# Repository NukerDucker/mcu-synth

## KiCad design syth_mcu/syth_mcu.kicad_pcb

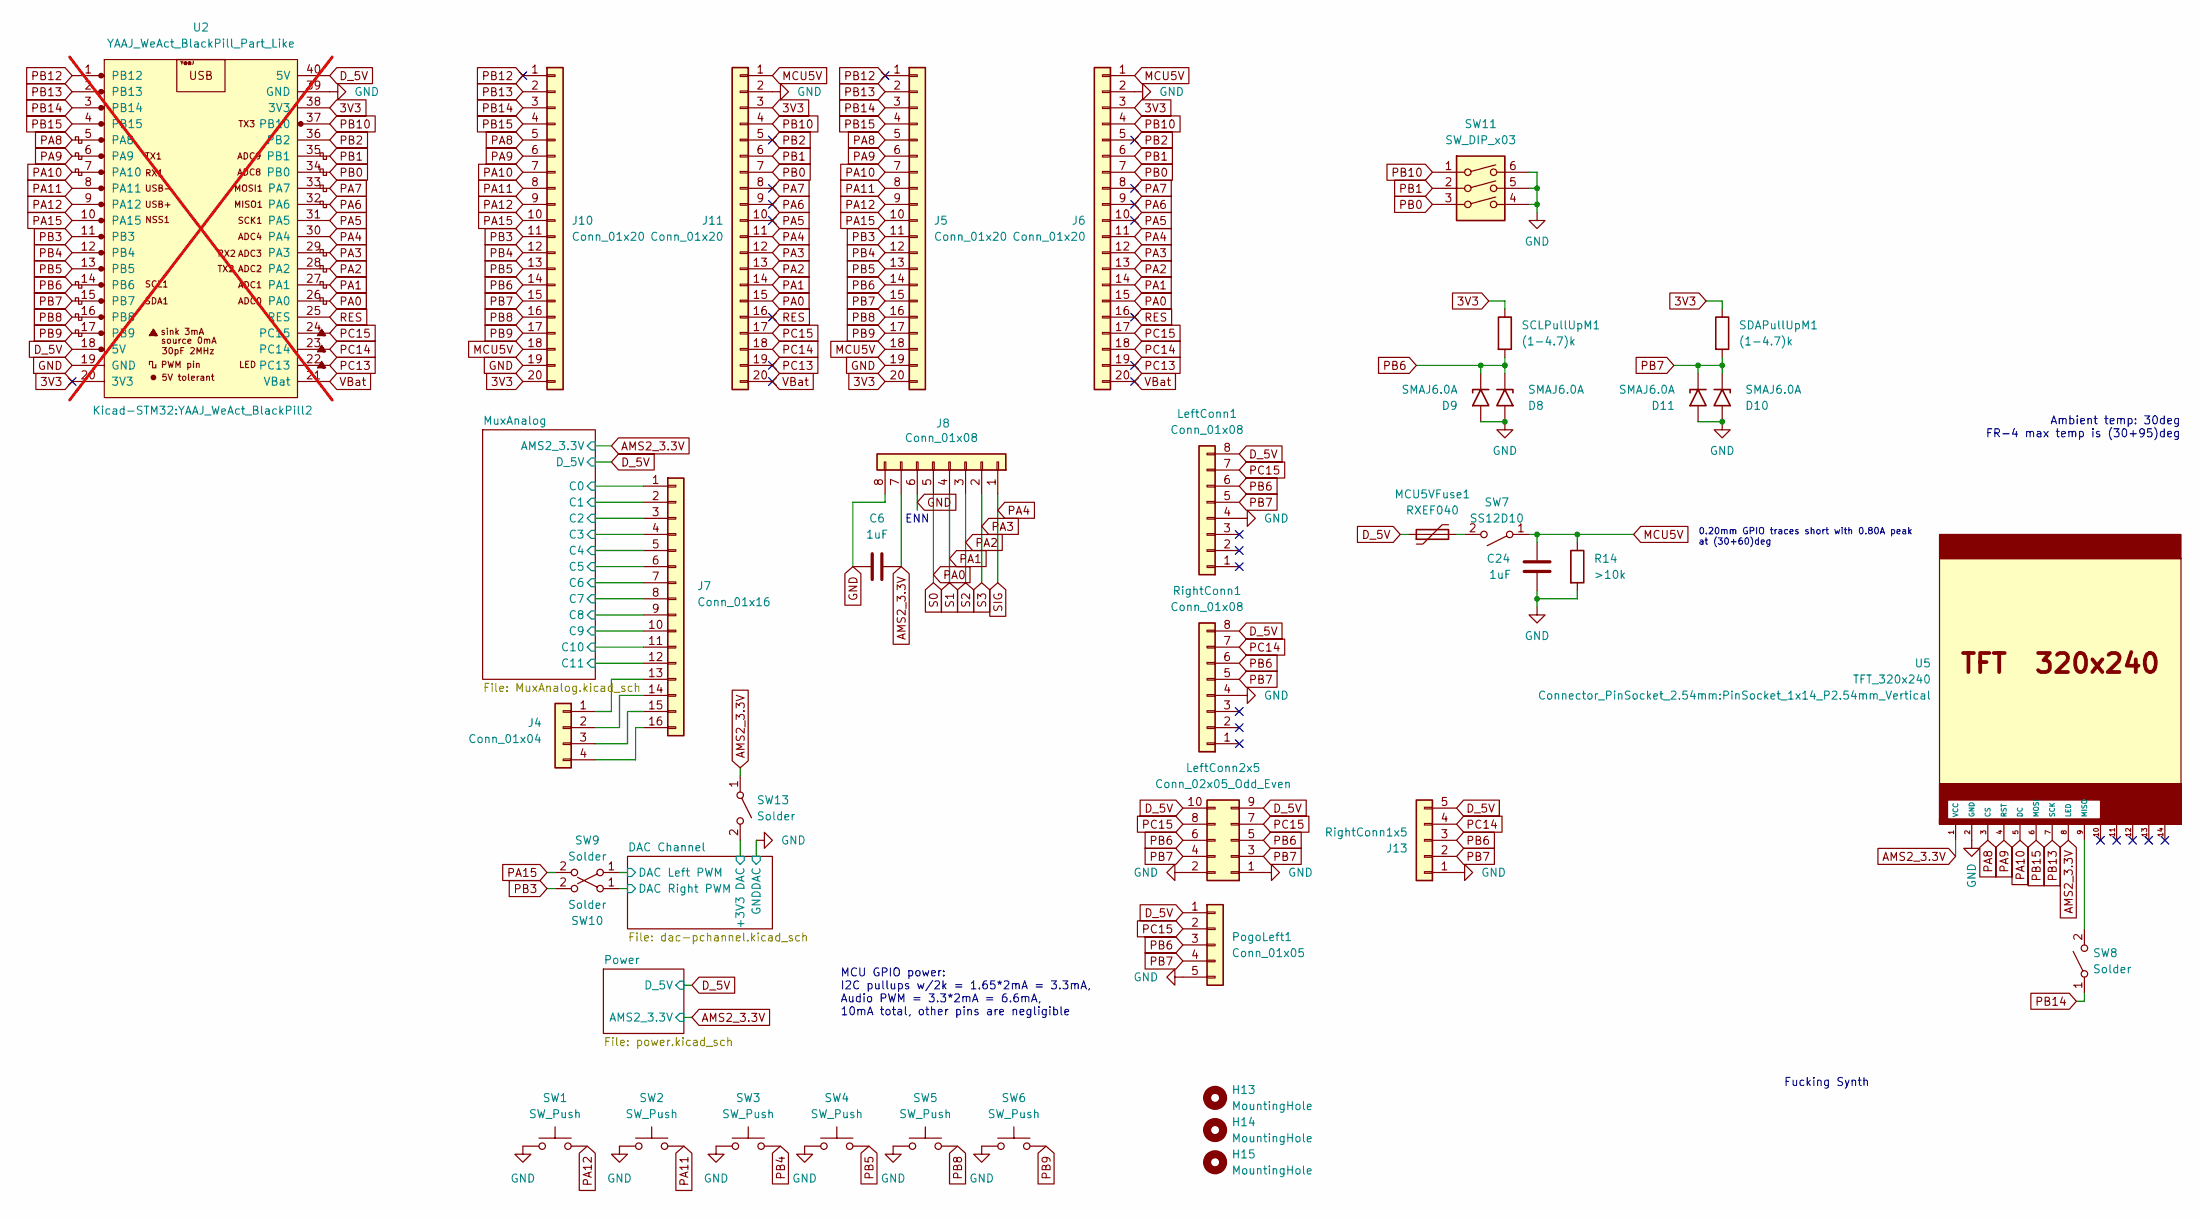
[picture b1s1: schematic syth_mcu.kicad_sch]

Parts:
C6, C24: 1uF; C_Disc_D5.0mm_W2.5mm_P5.00mm
D8, D9, D10, D11: SMAJ6.0A; D_SMA
H13, H14, H15: MountingHole; MountingHole_3.2mm_M3
J4: Conn_01x04; PinHeader_1x04_P2.54mm_Vertical
J5, J6: Conn_01x20; PinHeader_1x20_P2.54mm_Vertical
J7: Conn_01x16; PinSocket_1x16_P2.54mm_Vertical
J8: Conn_01x08; PinSocket_1x08_P2.54mm_Vertical
J10, J11: Conn_01x20; PinSocket_1x20_P2.54mm_Vertical
J13: RightConn1x5; PinSocket_1x05_P2.54mm_Horizontal
LeftConn1: Conn_01x08; PinSocket_1x08_P2.54mm_Horizontal
LeftConn2x5: Conn_02x05_Odd_Even; PinHeader_2x05_P2.54mm_Horizontal
MCU5VFuse1: RXEF040
PogoLeft1: Conn_01x05; CONN-TH_PR5L4015-5P-C-F
R14: >10k; R_Axial_DIN0207_L6.3mm_D2.5mm_P10.16mm_Horizontal
RightConn1: Conn_01x08; PinHeader_1x08_P2.54mm_Horizontal
SCLPullUpM1: (1-4.7)k; R_Axial_DIN0207_L6.3mm_D2.5mm_P10.16mm_Horizontal
SDAPullUpM1: (1-4.7)k; R_Axial_DIN0207_L6.3mm_D2.5mm_P10.16mm_Horizontal
SW1, SW2, SW3, SW4, SW5, SW6: SW_Push; SW_MX_HS_KS-2P02B01-01_1u
SW7: SS12D10
SW8, SW9, SW10, SW13: Solder; SolderJumper-2_P1.3mm_Open_Pad1.0x1.5mm
SW11: SW_DIP_x03; DIPSwitch3
U2: YAAJ_WeAct_BlackPill_Part_Like; YAAJ_WeAct_BlackPill2; not fitted
U5: TFT_320x240; PinSocket_1x14_P2.54mm_Vertical

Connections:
3V3: J5.20, J6.3, J10.20, J11.3, SCLPullUpM1.1, SDAPullUpM1.1, U2.20 (3V3), U2.38 (3V3)
/DAC Channel/+3V3 DAC: SW13.2 (B); also elsewhere on the board
/DAC Channel/DAC Left PWM: SW9.1 (A); also elsewhere on the board
/DAC Channel/DAC Right PWM: SW10.1 (A); also elsewhere on the board
/MuxAnalog/C0: J7.1; also elsewhere on the board
/MuxAnalog/C1: J7.2; also elsewhere on the board
/MuxAnalog/C2: J7.3; also elsewhere on the board
/MuxAnalog/C3: J7.4; also elsewhere on the board
/MuxAnalog/C4: J7.5; also elsewhere on the board
/MuxAnalog/C5: J7.6; also elsewhere on the board
/MuxAnalog/C6: J7.7; also elsewhere on the board
/MuxAnalog/C7: J7.8; also elsewhere on the board
/MuxAnalog/C8: J7.9; also elsewhere on the board
/MuxAnalog/C9: J7.10; also elsewhere on the board
/MuxAnalog/C10: J7.11; also elsewhere on the board
/MuxAnalog/C11: J7.12; also elsewhere on the board
AMS2_3.3V: C6.2, J8.7, SW13.1 (A), U5.1 (VCC), U5.8 (LED); also elsewhere on the board
D_5V: J13.5, LeftConn1.8, LeftConn2x5.9, LeftConn2x5.10, MCU5VFuse1.1, PogoLeft1.1, RightConn1.8, U2.18 (5V), U2.40 (5V); also elsewhere on the board
GND: C6.1, C24.2, D8.2 (A2), D9.2 (A2), D10.2 (A2), D11.2 (A2), J5.19, J6.2, J8.6, J8.8, J10.19, J11.2, J13.1, LeftConn1.4, LeftConn2x5.1, LeftConn2x5.2, PogoLeft1.5, R14.2, RightConn1.4, SW1.1, SW2.1, SW3.1, SW4.1, SW5.1, SW6.1, SW11.4, SW11.5, SW11.6, U2.19 (GND), U2.39 (GND), U5.2 (GND); also elsewhere on the board
MCU5V: C24.1, J5.18, J6.1, J10.18, J11.1, R14.1, SW7.1 (A)
unnamed: J4.1, J7.13
unnamed: J4.2, J7.14
unnamed: J4.3, J7.15
unnamed: J4.4, J7.16
unnamed: MCU5VFuse1.2, SW7.2 (B)
unnamed: SW8.2 (B), U5.9 (MISO)
PA0: J6.15, J8.5, J11.15, U2.26 (PA0)
PA1: J6.14, J8.4, J11.14, U2.27 (PA1)
PA2: J6.13, J8.3, J11.13, U2.28 (PA2)
PA3: J6.12, J8.2, J11.12, U2.29 (PA3)
PA4: J6.11, J8.1, J11.11, U2.30 (PA4)
PA5: J6.10, J11.10, U2.31 (PA5)
PA6: J6.9, J11.9, U2.32 (PA6)
PA7: J6.8, J11.8, U2.33 (PA7)
PA8: J5.5, J10.5, U2.5 (PA8), U5.3 (CS)
PA9: J5.6, J10.6, U2.6 (PA9), U5.4 (RST)
PA10: J5.7, J10.7, U2.7 (PA10), U5.5 (DC)
PA11: J5.8, J10.8, SW2.2, U2.8 (PA11)
PA12: J5.9, J10.9, SW1.2, U2.9 (PA12)
PA15: J5.10, J10.10, SW9.2 (B), U2.10 (PA15)
PB0: J6.7, J11.7, SW11.3, U2.34 (PB0)
PB1: J6.6, J11.6, SW11.2, U2.35 (PB1)
PB2: J6.5, J11.5, U2.36 (PB2)
PB3: J5.11, J10.11, SW10.2 (B), U2.11 (PB3)
PB4: J5.12, J10.12, SW3.2, U2.12 (PB4)
PB5: J5.13, J10.13, SW4.2, U2.13 (PB5)
PB6: D8.1 (A1), D9.1 (A1), J5.14, J10.14, J13.3, LeftConn1.6, LeftConn2x5.5, LeftConn2x5.6, PogoLeft1.3, RightConn1.6, SCLPullUpM1.2, U2.14 (PB6)
PB7: D10.1 (A1), D11.1 (A1), J5.15, J10.15, J13.2, LeftConn1.5, LeftConn2x5.3, LeftConn2x5.4, PogoLeft1.4, RightConn1.5, SDAPullUpM1.2, U2.15 (PB7)
PB8: J5.16, J10.16, SW5.2, U2.16 (PB8)
PB9: J5.17, J10.17, SW6.2, U2.17 (PB9)
PB10: J6.4, J11.4, SW11.1, U2.37 (PB10)
PB12: J5.1, J10.1, U2.1 (PB12)
PB13: J5.2, J10.2, U2.2 (PB13), U5.7 (SCK)
PB14: J5.3, J10.3, SW8.1 (A), U2.3 (PB14)
PB15: J5.4, J10.4, U2.4 (PB15), U5.6 (MOSI)
PC13: J6.19, J11.19, U2.22 (PC13)
PC14: J6.18, J11.18, J13.4, RightConn1.7, U2.23 (PC14)
PC15: J6.17, J11.17, LeftConn1.7, LeftConn2x5.7, LeftConn2x5.8, PogoLeft1.2, U2.24 (PC15)
RES: J6.16, J11.16, U2.25 (RES)
VBat: J6.20, J11.20, U2.21 (VBat)

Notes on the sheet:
Ambient temp: 30deg FR-4 max temp is (30+95)deg
MCU GPIO power: I2C pullups w/2k = 1.65*2mA = 3.3mA, Audio PWM = 3.3*2mA = 6.6mA, 10mA total, other pins are negligible
ENN
Fucking Synth
0.20mm GPIO traces short with 0.80A peak at (30+60)deg

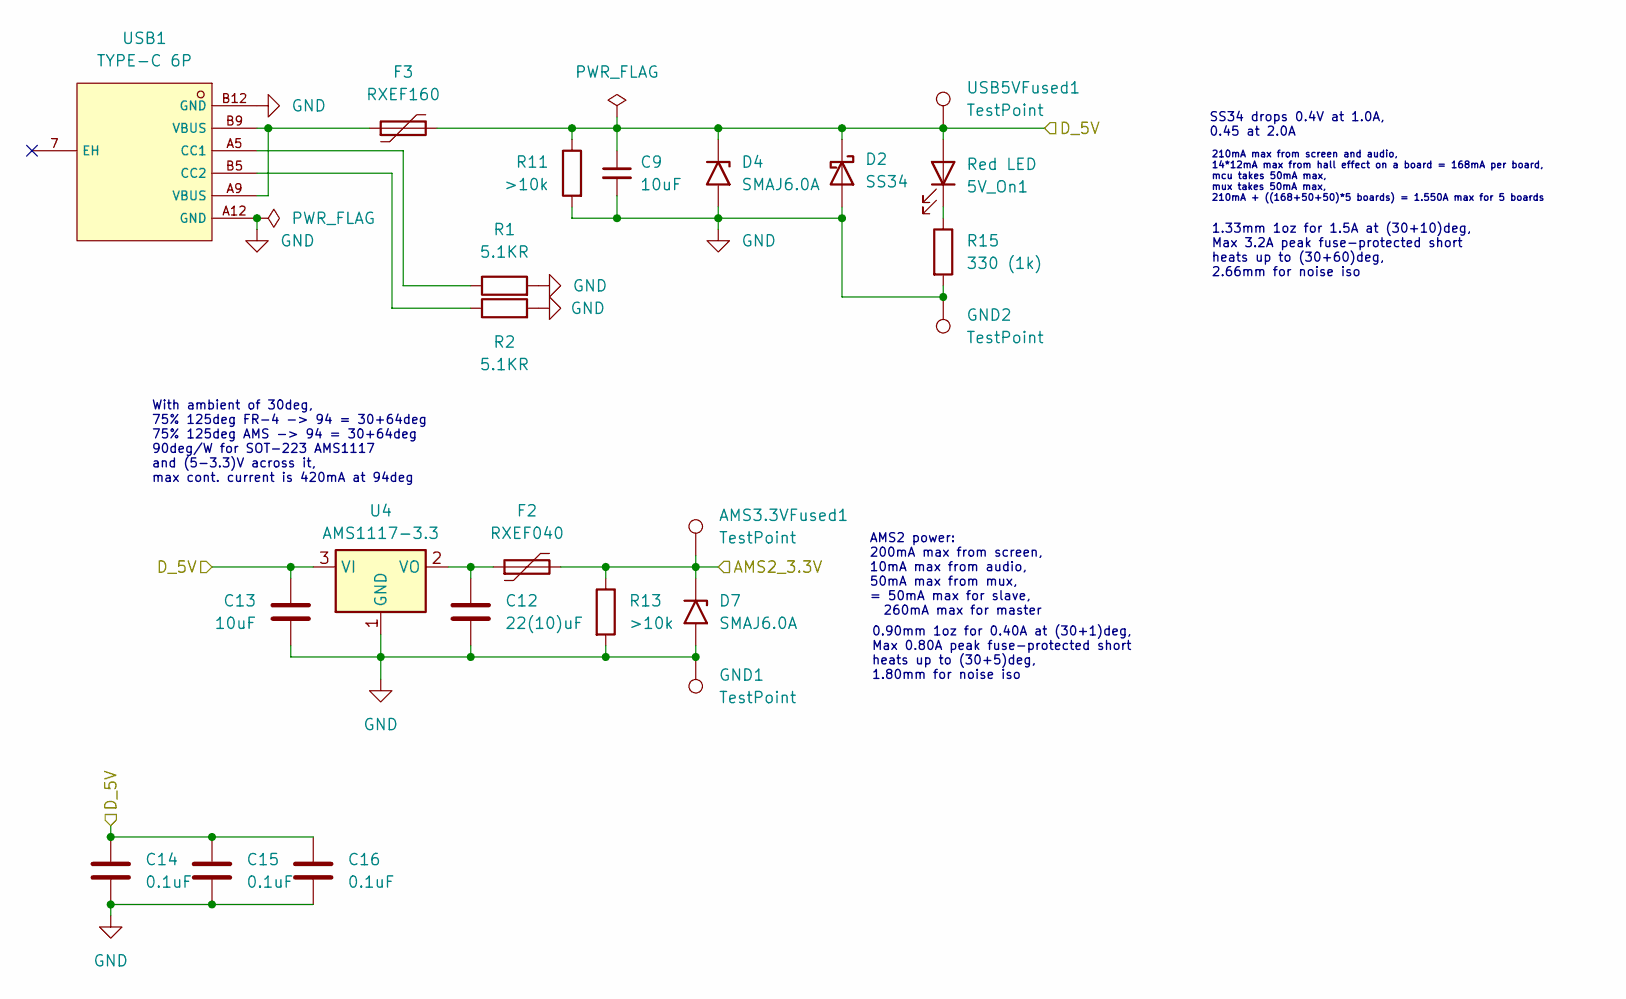
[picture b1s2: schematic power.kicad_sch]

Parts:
5V_On1: Red LED; LED_D3.0mm
AMS3.3VFused1: TestPoint; PinHeader_1x02_P2.54mm_Vertical
C9, C13: 10uF; CP_Radial_D4.0mm_P2.00mm
C12: 22(10)uF; CP_Radial_D4.0mm_P2.00mm
C14, C15, C16: 0.1uF; C_Disc_D5.0mm_W2.5mm_P5.00mm
D2: SS34; D_SMA
D4, D7: SMAJ6.0A; D_SMA
F2: RXEF040
F3: RXEF160
GND1, GND2: TestPoint; PinHeader_1x02_P2.54mm_Vertical
R1, R2: 5.1KR; R_Axial_DIN0207_L6.3mm_D2.5mm_P10.16mm_Horizontal
R11, R13: >10k; R_Axial_DIN0207_L6.3mm_D2.5mm_P10.16mm_Horizontal
R15: 330 (1k); R_Axial_DIN0207_L6.3mm_D2.5mm_P10.16mm_Horizontal
U4: AMS1117-3.3; TO-252-3_TabPin2_HandSolder
USB1: TYPE-C 6P; C456012_TYPE-C-SMD_TYPE-C-6P_1; LCSC C456012
USB5VFused1: TestPoint; PinHeader_1x02_P2.54mm_Vertical

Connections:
AMS2_3.3V: AMS3.3VFused1.1 (1_1), D7.1 (A1), F2.2, R13.1; also elsewhere on the board
D_5V: 5V_On1.2 (A), C9.1, C13.2, C14.2, C15.2, C16.2, D2.1 (K), D4.1 (A1), F3.2, R11.1, U4.3 (VI), USB5VFused1.1 (1_1); also elsewhere on the board
GND: C9.2, C12.1, C13.1, C14.1, C15.1, C16.1, D2.2 (A), D4.2 (A2), D7.2 (A2), GND1.1 (1_1), GND2.1 (1_1), R1.2, R2.2, R11.2, R13.2, R15.2, U4.1 (GND), USB1.A12 (GND), USB1.B12 (GND); also elsewhere on the board
unnamed: 5V_On1.1 (K), R15.1
unnamed: F3.1, USB1.A9 (VBUS), USB1.B9 (VBUS)
unnamed: C12.2, F2.1, U4.2 (VO)
unnamed: R1.1, USB1.A5 (CC1)
unnamed: R2.1, USB1.B5 (CC2)

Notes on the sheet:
AMS2 power: 200mA max from screen, 10mA max from audio, 50mA max from mux, = 50mA max for slave, 260mA max for master
1.33mm 1oz for 1.5A at (30+10)deg, Max 3.2A peak fuse-protected short heats up to (30+60)deg, 2.66mm for noise iso
With ambient of 30deg, 75% 125deg FR-4 -> 94 = 30+64deg 75% 125deg AMS -> 94 = 30+64deg 90deg/W for SOT-223 AMS1117 and (5-3.3)V across it, max cont. current is 420mA at 94deg
SS34 drops 0.4V at 1.0A, 0.45 at 2.0A
210mA max from screen and audio, 14*12mA max from hall effect on a board = 168mA per board, mcu takes 50mA max, mux takes 50mA max, 210mA + ((168+50+50)*5 boards) = 1.550A max for 5 boards
0.90mm 1oz for 0.40A at (30+1)deg, Max 0.80A peak fuse-protected short heats up to (30+5)deg, 1.80mm for noise iso

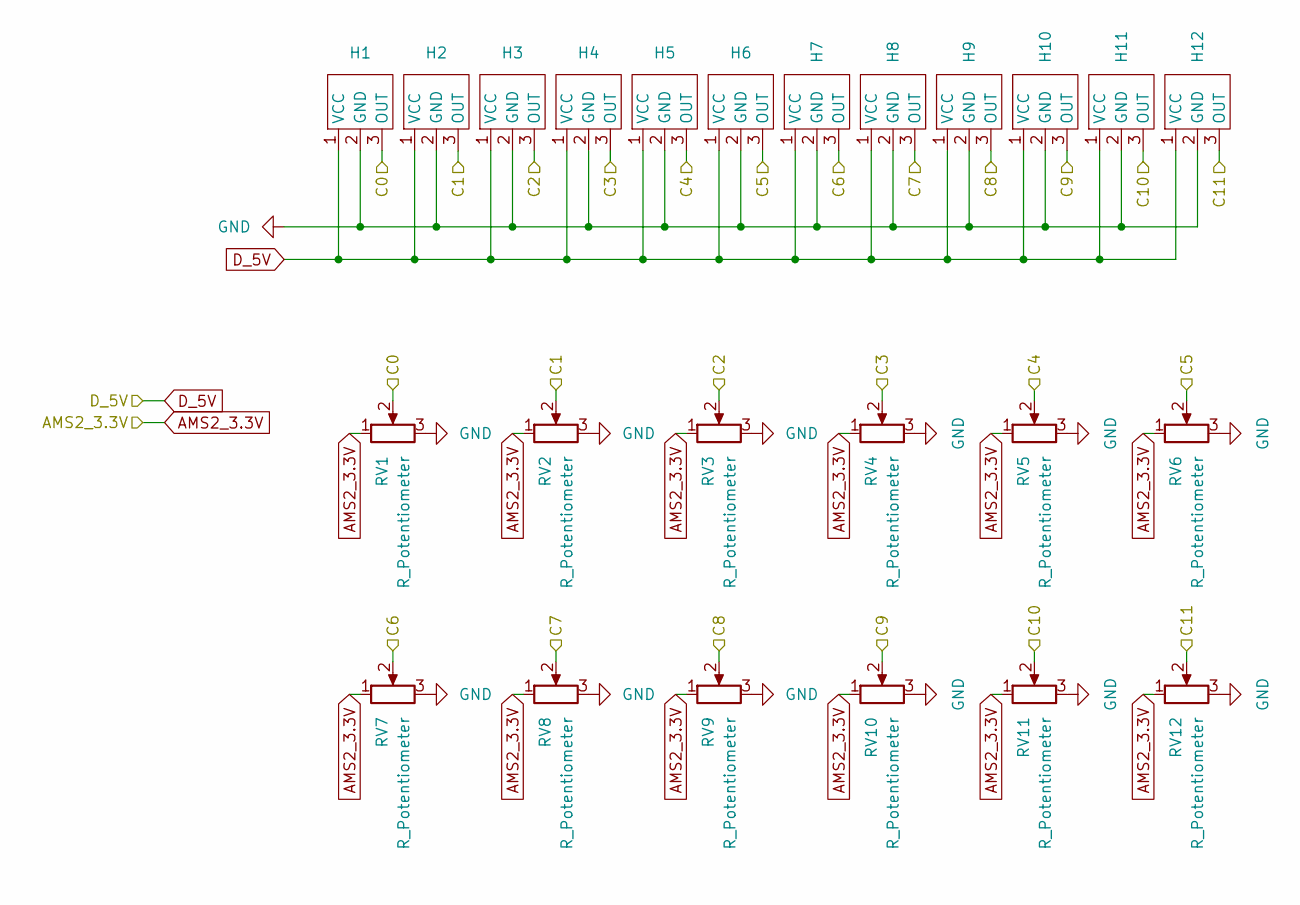
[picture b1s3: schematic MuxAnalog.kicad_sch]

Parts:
H1, H2, H3, H4, H5, H6, H7, H8, H9, H10, H11, H12: TO-92_Inline_AH3503
RV1, RV2, RV3, RV4, RV5, RV6, RV7, RV8, RV9, RV10, RV11, RV12: R_Potentiometer; Potentiometer_Alps_RK09K_Single_Vertical

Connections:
/MuxAnalog/C0: H1.3 (OUT), RV1.2; also elsewhere on the board
/MuxAnalog/C1: H2.3 (OUT), RV2.2; also elsewhere on the board
/MuxAnalog/C2: H3.3 (OUT), RV3.2; also elsewhere on the board
/MuxAnalog/C3: H4.3 (OUT), RV4.2; also elsewhere on the board
/MuxAnalog/C4: H5.3 (OUT), RV5.2; also elsewhere on the board
/MuxAnalog/C5: H6.3 (OUT), RV6.2; also elsewhere on the board
/MuxAnalog/C6: H7.3 (OUT), RV7.2; also elsewhere on the board
/MuxAnalog/C7: H8.3 (OUT), RV8.2; also elsewhere on the board
/MuxAnalog/C8: H9.3 (OUT), RV9.2; also elsewhere on the board
/MuxAnalog/C9: H10.3 (OUT), RV10.2; also elsewhere on the board
/MuxAnalog/C10: H11.3 (OUT), RV11.2; also elsewhere on the board
/MuxAnalog/C11: H12.3 (OUT), RV12.2; also elsewhere on the board
AMS2_3.3V: RV1.1, RV2.1, RV3.1, RV4.1, RV5.1, RV6.1, RV7.1, RV8.1, RV9.1, RV10.1, RV11.1, RV12.1; also elsewhere on the board
D_5V: H1.1 (VCC), H2.1 (VCC), H3.1 (VCC), H4.1 (VCC), H5.1 (VCC), H6.1 (VCC), H7.1 (VCC), H8.1 (VCC), H9.1 (VCC), H10.1 (VCC), H11.1 (VCC), H12.1 (VCC); also elsewhere on the board
GND: H1.2 (GND), H2.2 (GND), H3.2 (GND), H4.2 (GND), H5.2 (GND), H6.2 (GND), H7.2 (GND), H8.2 (GND), H9.2 (GND), H10.2 (GND), H11.2 (GND), H12.2 (GND), RV1.3, RV2.3, RV3.3, RV4.3, RV5.3, RV6.3, RV7.3, RV8.3, RV9.3, RV10.3, RV11.3, RV12.3; also elsewhere on the board

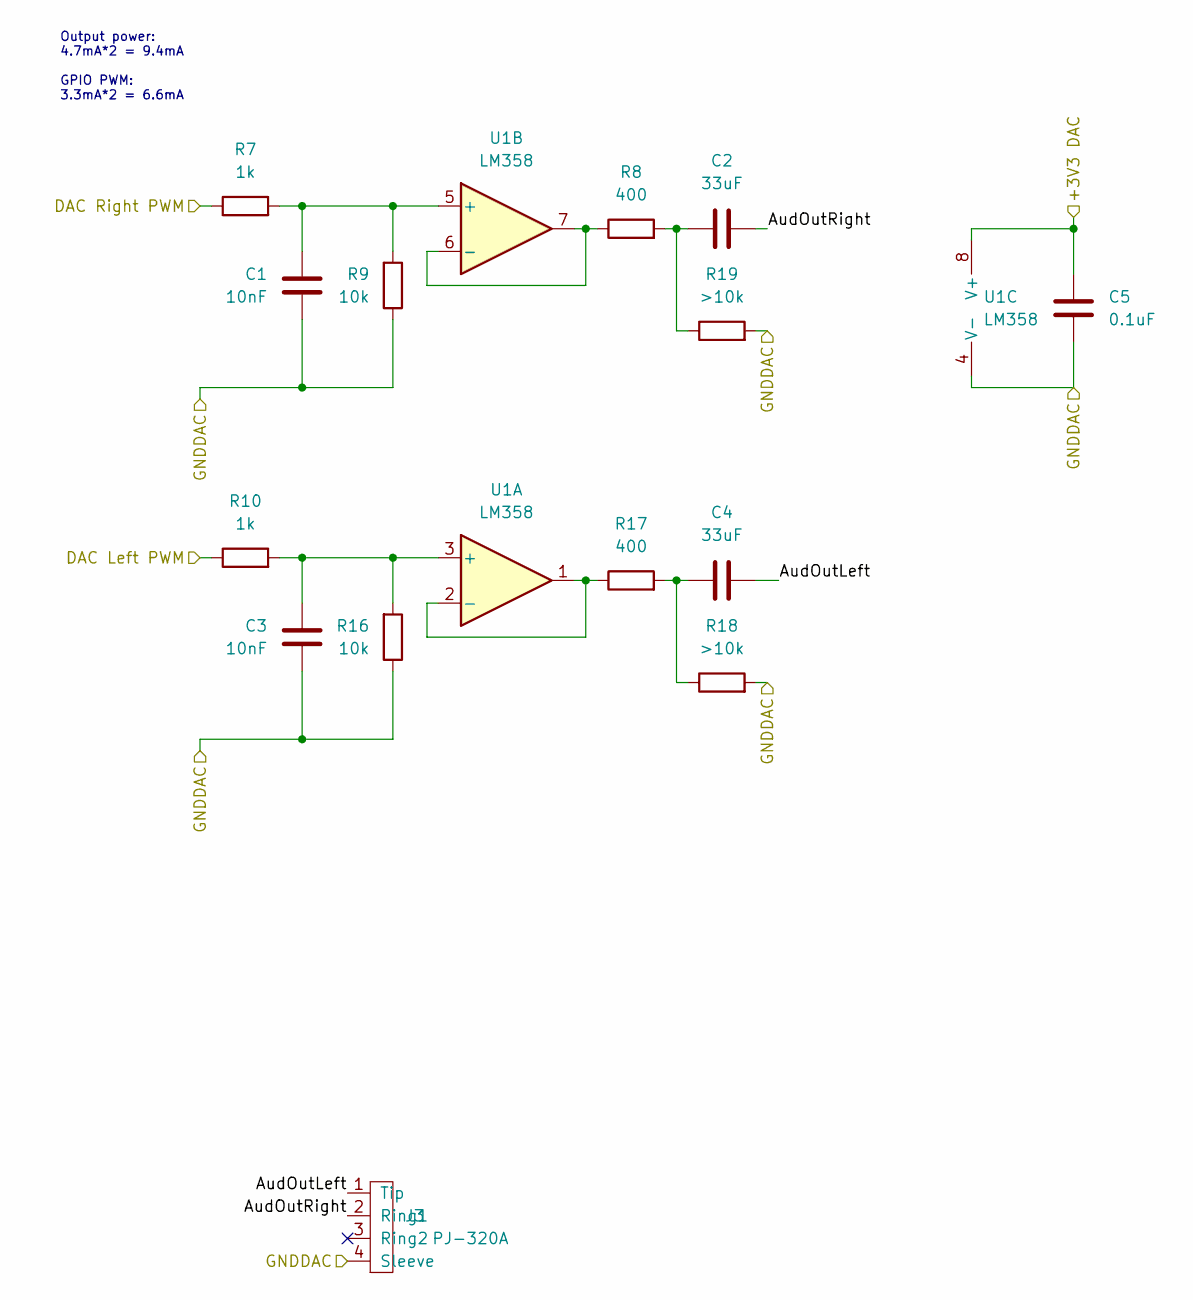
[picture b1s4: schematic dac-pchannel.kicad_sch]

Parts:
C1, C3: 10nF; C_Disc_D5.0mm_W2.5mm_P5.00mm
C2, C4: 33uF; CP_Radial_D4.0mm_P2.00mm
C5: 0.1uF; C_Disc_D5.0mm_W2.5mm_P5.00mm
J3: PJ-320A; TRRS-PJ-320A
R7, R10: 1k; R_Axial_DIN0207_L6.3mm_D2.5mm_P10.16mm_Horizontal
R8, R17: 400; R_Axial_DIN0207_L6.3mm_D2.5mm_P10.16mm_Horizontal
R9, R16: 10k; R_Axial_DIN0207_L6.3mm_D2.5mm_P10.16mm_Horizontal
R18, R19: >10k; R_Axial_DIN0207_L6.3mm_D2.5mm_P10.16mm_Horizontal
U1: LM358; DIP-8_W7.62mm

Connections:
/DAC Channel/+3V3 DAC: C5.1, U1.8 (V+); also elsewhere on the board
/DAC Channel/AudOutLeft: C4.2, J3.1 (Tip)
/DAC Channel/AudOutRight: C2.2, J3.2 (Ring1)
/DAC Channel/DAC Left PWM: R10.1; also elsewhere on the board
/DAC Channel/DAC Right PWM: R7.1; also elsewhere on the board
GND: C1.2, C3.2, C5.2, J3.4 (Sleeve), R9.1, R16.1, R18.2, R19.2, U1.4 (V-); also elsewhere on the board
unnamed: C2.1, R8.2, R19.1
unnamed: C4.1, R17.2, R18.1
unnamed: C3.1, R10.2, R16.2, U1.3 (+)
unnamed: R17.1, U1.1, U1.2 (-)
unnamed: C1.1, R7.2, R9.2, U1.5 (+)
unnamed: R8.1, U1.6 (-), U1.7

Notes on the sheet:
Output power: 4.7mA*2 = 9.4mA GPIO PWM: 3.3mA*2 = 6.6mA

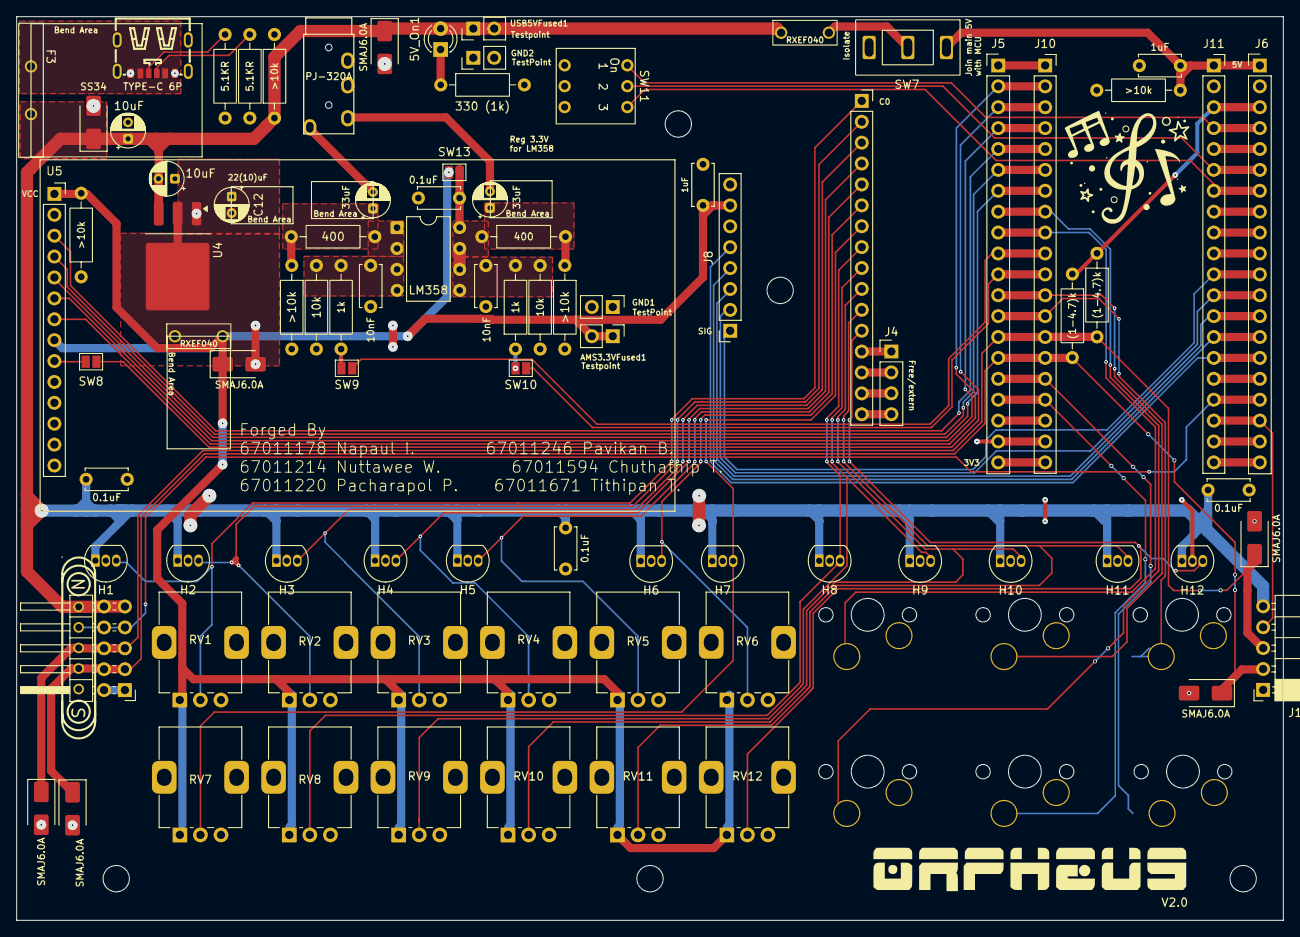
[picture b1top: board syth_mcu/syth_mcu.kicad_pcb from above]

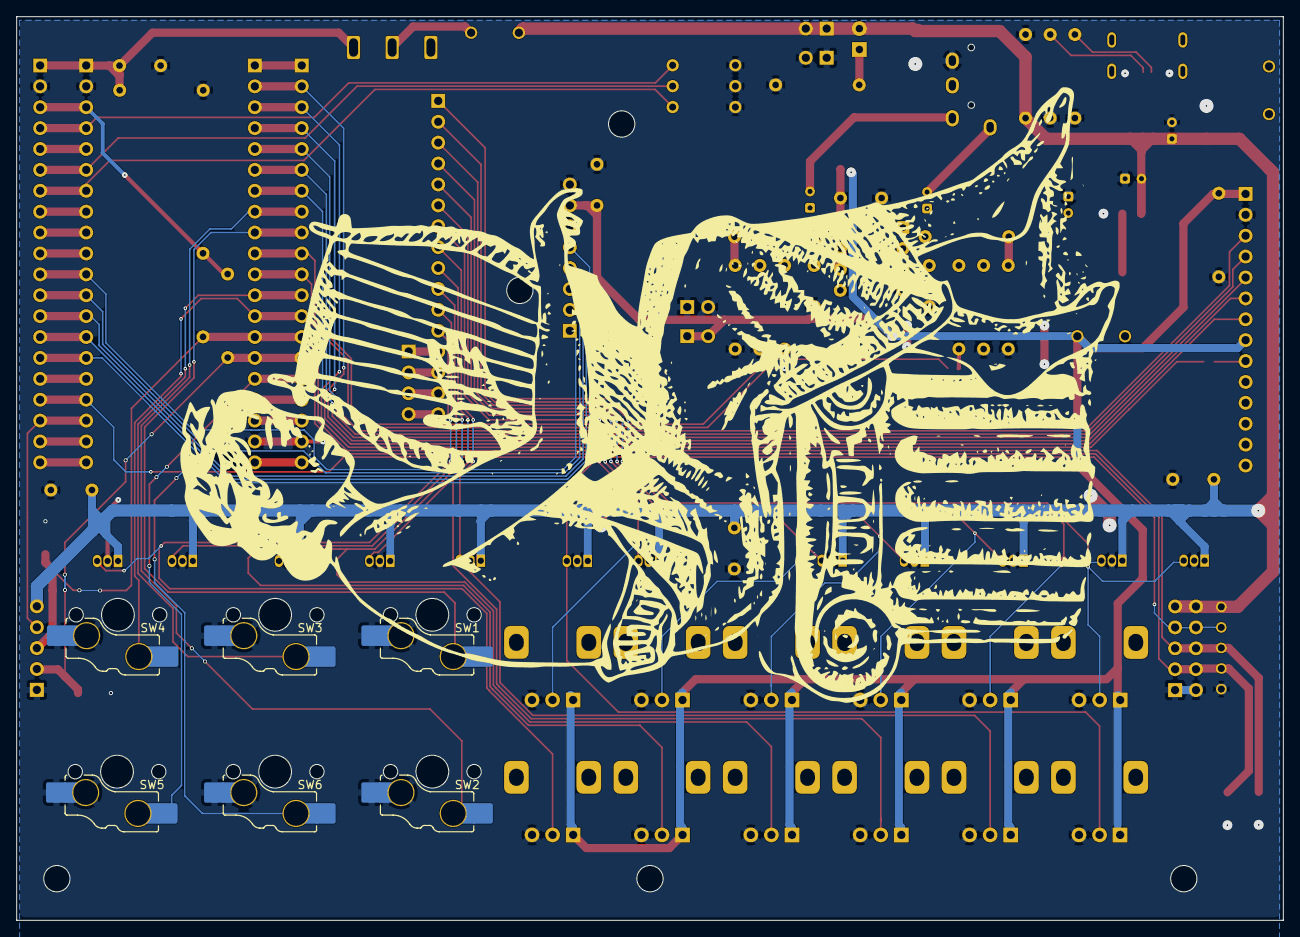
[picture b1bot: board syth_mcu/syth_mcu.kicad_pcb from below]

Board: 2 copper layers, 154.0 x 109.9 mm, 100 parts (6 on the bottom side), 73 nets.

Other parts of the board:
H14#2, H14#3: MountingHole; MountingHole_3.2mm_M3

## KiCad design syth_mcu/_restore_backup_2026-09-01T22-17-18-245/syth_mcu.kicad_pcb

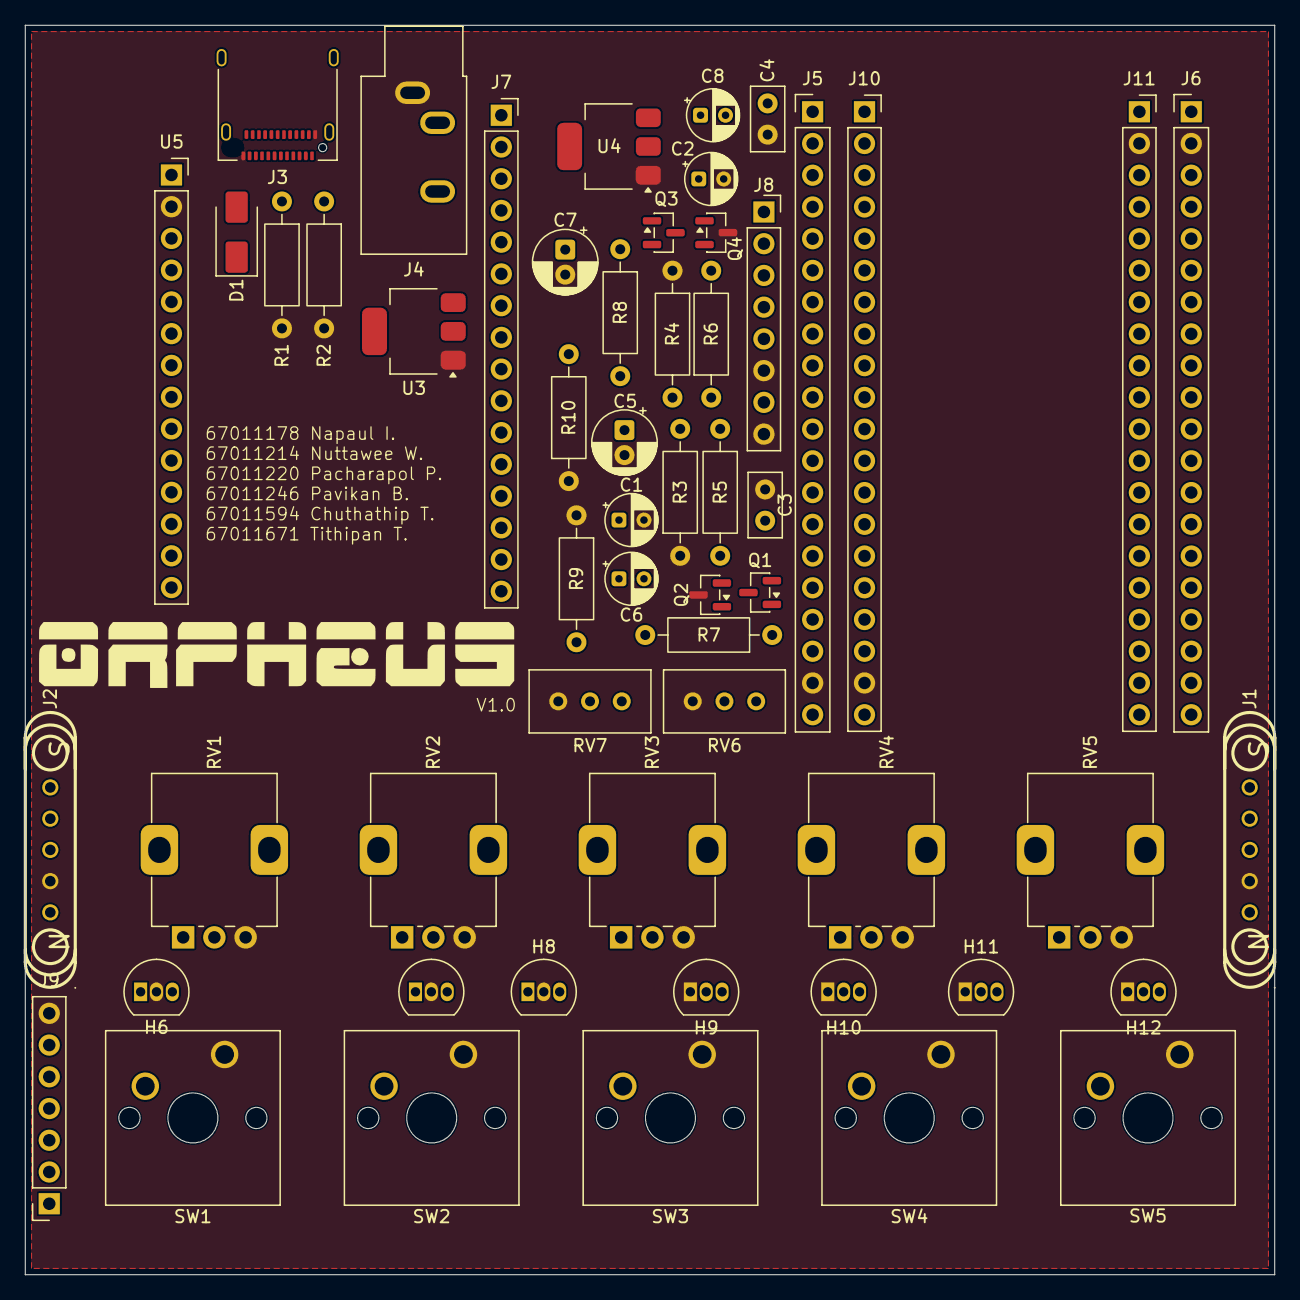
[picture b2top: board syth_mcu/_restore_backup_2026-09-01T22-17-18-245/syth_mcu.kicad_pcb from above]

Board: 2 copper layers, 100.0 x 100.0 mm, 56 parts (0 on the bottom side), 64 nets, no tracks yet.

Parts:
C1, C2: 80nF; CP_Radial_D4.0mm_P2.00mm
C3, C4: 0.1uF C; C_Disc_D5.0mm_W2.5mm_P2.50mm
C5, C7: 1uF; CP_Radial_D5.0mm_P2.00mm
C6, C8: 33uF; CP_Radial_D4.0mm_P2.00mm
D1: SS14; D_SMA
H6, H7, H8, H9, H10, H11, H12: TO-92_Inline
J1, J2: Conn_01x05; CONN-TH_PR5L4015-5P-C-F
J3: USB_C_Receptacle_PowerOnly_6P; USB_C_Receptacle_Amphenol_12401610E4-2A
J4: AudioPlug3; Jack_3.5mm_CUI_SJ1-3533NG_Horizontal
J5, J6: Conn_01x20; PinHeader_1x20_P2.54mm_Vertical
J7: Conn_01x16; PinSocket_1x16_P2.54mm_Vertical
J8: Conn_01x08; PinSocket_1x08_P2.54mm_Vertical
J9: Conn_01x07; PinSocket_1x07_P2.54mm_Vertical
J10, J11: Conn_01x20; PinSocket_1x20_P2.54mm_Vertical
Q1, Q3: SI2307DS; SOT-23
Q2, Q4: SI2304DS; SOT-23
R1, R2: 5.1KR; R_Axial_DIN0207_L6.3mm_D2.5mm_P10.16mm_Horizontal
R3, R4, R9, R10: 10k; R_Axial_DIN0207_L6.3mm_D2.5mm_P10.16mm_Horizontal
R5, R6: 2k; R_Axial_DIN0207_L6.3mm_D2.5mm_P10.16mm_Horizontal
R7, R8: 100 1%; R_Axial_DIN0207_L6.3mm_D2.5mm_P10.16mm_Horizontal
RV1, RV2, RV3, RV4, RV5: R_Potentiometer; Potentiometer_Alps_RK09K_Single_Vertical
RV6, RV7: 100k; Potentiometer_Bourns_3296W_Vertical
SW1, SW2, SW3, SW4, SW5: SW_Push; SW_Cherry_MX_1.00u_PCB
U3, U4: AMS1117-3.3; SOT-223-3_TabPin2
U5: TFT_320x240; PinSocket_1x14_P2.54mm_Vertical

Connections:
3V3: J5.20, J6.3, J10.20, J11.3
/DAC Channel/AudOutLeft: J4.T, RV7.2
/DAC Channel/AudOutRight: J4.R, RV6.2
AMS1_3.3V: H6.1 (VCC), H7.1 (VCC), H8.1 (VCC), H9.2 (GND), H10.2 (GND), H11.2 (GND), H12.2 (GND), J8.7, J9.6, RV1.1, RV2.1, RV3.1, RV4.1, RV5.1, U3.2 (VO)
AMS2_3.3V: C3.1, C4.1, C5.1, C7.1, Q1.3 (S), Q3.3 (S), U4.2 (VO), U5.1 (VCC), U5.8 (LED)
C0: J7.16, J9.1
C1: J7.15, J9.2
C2: J7.14, J9.3
C3: J7.13, J9.4
C4: J7.12, J9.5
C5: H6.3 (OUT), J7.11
C6: H7.3 (OUT), J7.10
C7: H8.3 (OUT), J7.9
C8: H9.3 (OUT), J7.8
C9: H10.3 (OUT), J7.7
C10: H11.3 (OUT), J7.6
C11: H12.3 (OUT), J7.5
D_5V: D1.1 (K), J1.1, J2.1, J5.18, J6.1, J10.18, J11.1, U3.3 (VI), U4.3 (VI)
ENN: C1.2, C2.2, C3.2, C4.2, C5.2, C7.2, H6.2 (GND), H7.2 (GND), H8.2 (GND), H9.1 (VCC), H10.1 (VCC), H11.1 (VCC), H12.1 (VCC), J1.2, J2.2, J3.A12 (GND), J3.B12 (GND), J4.S, J5.19, J6.2, J8.6, J8.8, J9.7, J10.19, J11.2, Q2.3 (S), Q4.3 (S), R1.2, R2.2, R3.1, R4.1, R9.1, R10.1, RV1.3, RV2.3, RV3.3, RV4.3, RV5.3, RV6.3, RV7.3, SW1.1, SW2.1, SW3.1, SW4.1, SW5.1, U3.1 (GND), U4.1 (GND), U5.2 (GND)
unnamed: C1.1, C6.1, R7.2, R9.2
unnamed: C2.1, C8.1, R8.2, R10.2
unnamed: C6.2, RV6.1
unnamed: C8.2, RV7.1
unnamed: D1.2 (A), J3.A9 (VBUS), J3.B9 (VBUS)
unnamed: J3.A5 (CC1), R1.1
unnamed: J3.B5 (CC2), R2.1
unnamed: Q1.1 (D), Q2.1 (D), R7.1
unnamed: Q1.2 (G), Q2.2 (G), R5.2
unnamed: Q3.1 (D), Q4.1 (D), R8.1
unnamed: Q3.2 (G), Q4.2 (G), R6.2
PA0: J6.15, J11.15, RV1.2
PA1: J6.14, J11.14, RV2.2
PA2: J6.13, J11.13, RV3.2
PA3: J6.12, J11.12, RV4.2
PA4: J6.11, J11.11, RV5.2
PA5: J6.10, J11.10, U5.7 (SCK)
PA6: J6.9, J11.9
PA7: J6.8, J11.8, U5.6 (MOSI)
PA8: J5.5, J10.5, U5.3 (CS)
PA9: J5.6, J10.6, U5.4 (RST)
PA10: J5.7, J10.7, U5.5 (DC)
PA11: J2.5, J5.8, J10.8
PA12: J1.5, J5.9, J10.9
PA15: J5.10, J10.10, R4.2, R6.1
PB0: J6.7, J8.1, J11.7
PB1: J6.6, J11.6
PB2: J6.5, J8.4, J11.5
PB3: J5.11, J10.11, R3.2, R5.1
PB4: J5.12, J10.12, SW1.2
PB5: J5.13, J10.13, SW2.2
PB6: J1.4, J2.4, J5.14, J10.14
PB7: J1.3, J2.3, J5.15, J10.15
PB8: J5.16, J10.16, SW3.2
PB9: J5.17, J10.17, SW4.2
PB10: J6.4, J11.4
PB12: J5.1, J10.1, SW5.2
PB13: J5.2, J8.3, J10.2
PB14: J5.3, J8.2, J10.3
PB15: J5.4, J8.5, J10.4
PC13: J6.19, J11.19
PC14: J6.18, J11.18
PC15: J6.17, J11.17
RES: J6.16, J11.16
VBat: J6.20, J11.20
